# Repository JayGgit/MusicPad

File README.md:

## MusicPad

**Made for Hackclub's [Blueprint](blueprint.hackclub.com)**

A super simple music control pad.

Features:
- Skip track
- Rewind track
- Play / Pause
- Mute / Unmute
-  Display - Does nothing for right now. I might change it later to include playback info from the plugged in device.

**Full MusicPad**

**PCB:**

**3d Printed Case:**

**BOM:**
- 4x - Cherry MX Switches
- 1x - XIAO RP2040
- 1x - 128x32 0.91in OLED Display
- 4x - Blank DSA Keycaps
- 4x - M3x16 Bolts
- 4x - M3 Heatset
- (3d printed parts)

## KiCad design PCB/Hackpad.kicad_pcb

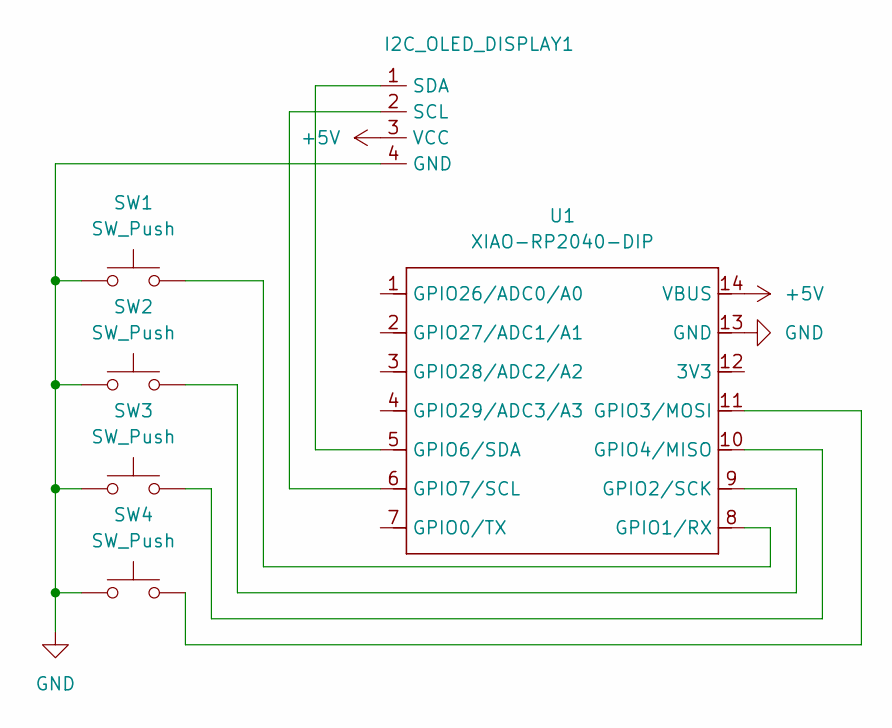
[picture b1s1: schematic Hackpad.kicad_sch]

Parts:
I2C_OLED_DISPLAY1: I2C_OLED_DISPLAY
SW1, SW2, SW3, SW4: SW_Push; SW_Cherry_MX_1.00u_PCB
U1: XIAO-RP2040-DIP

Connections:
+5V: I2C_OLED_DISPLAY1.3 (VCC), U1.14 (VBUS)
GND: I2C_OLED_DISPLAY1.4 (GND), SW1.1, SW2.1, SW3.1, SW4.1, U1.13 (GND)
unnamed: I2C_OLED_DISPLAY1.2 (SCL), U1.6 (GPIO7/SCL)
unnamed: I2C_OLED_DISPLAY1.1 (SDA), U1.5 (GPIO6/SDA)
unnamed: SW1.2, U1.8 (GPIO1/RX)
unnamed: SW2.2, U1.9 (GPIO2/SCK)
unnamed: SW4.2, U1.11 (GPIO3/MOSI)
unnamed: SW3.2, U1.10 (GPIO4/MISO)

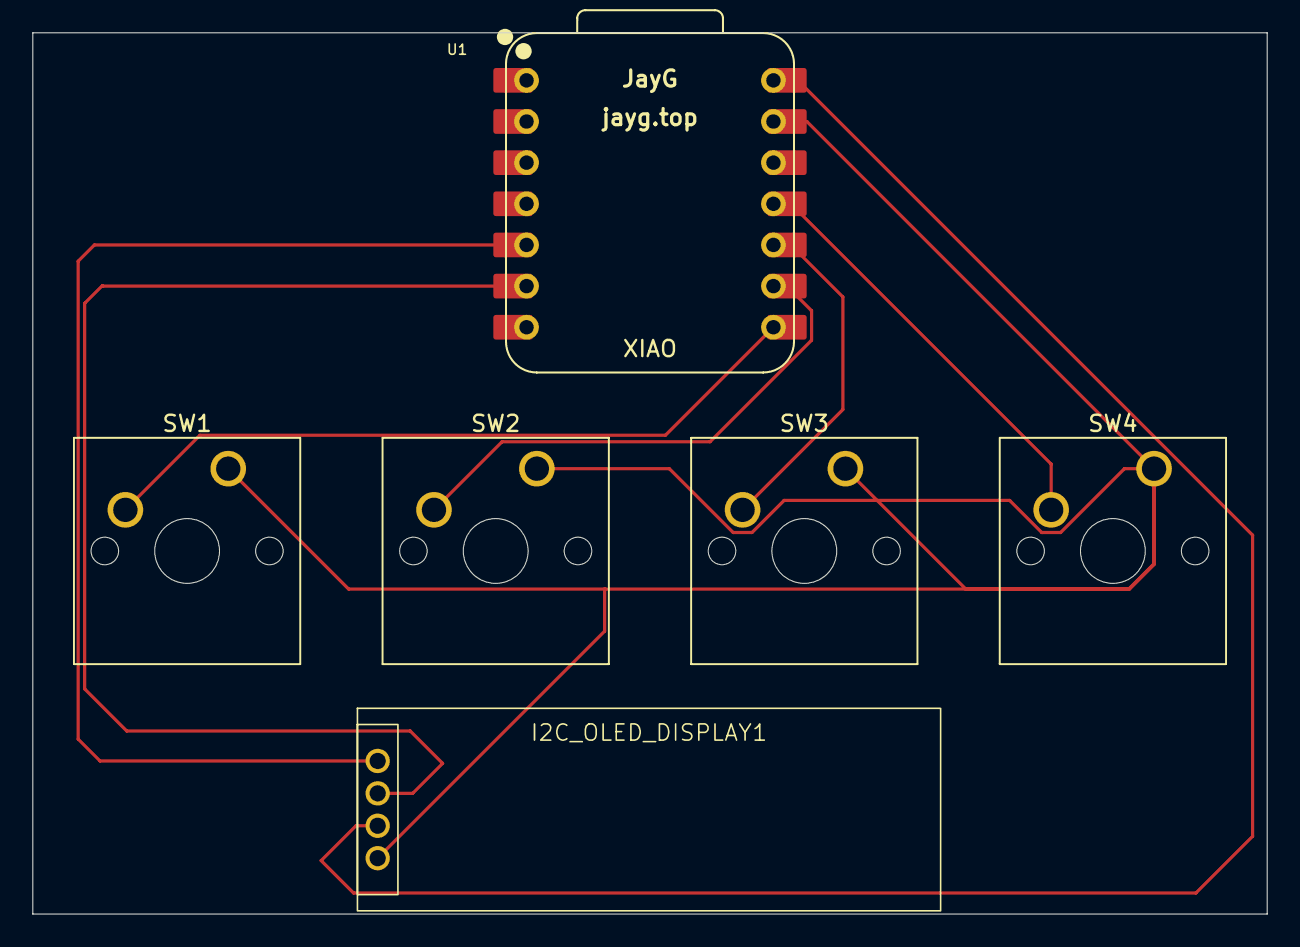
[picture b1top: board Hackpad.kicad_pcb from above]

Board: 2 copper layers, 76.2 x 54.4 mm, 6 parts (0 on the bottom side), 8 nets.

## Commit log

2025-11-27 Init
2025-11-27 README images
2025-11-27 Add README.md
2025-11-27 Added the stl's
2025-11-29 Added the actual case + PCB .step file
2025-11-29 Added PCB image
2025-11-29 Edit the case image to include the PCB
2025-12-27 Made the firmware actually work
2025-12-27 Remove filesystem for prod
2025-12-27 Added installable drivers
2026-01-04 Added real printed out images
2026-01-05 Added image of HackPad with the case
2026-01-05 Added images of the MusicPad in the README
